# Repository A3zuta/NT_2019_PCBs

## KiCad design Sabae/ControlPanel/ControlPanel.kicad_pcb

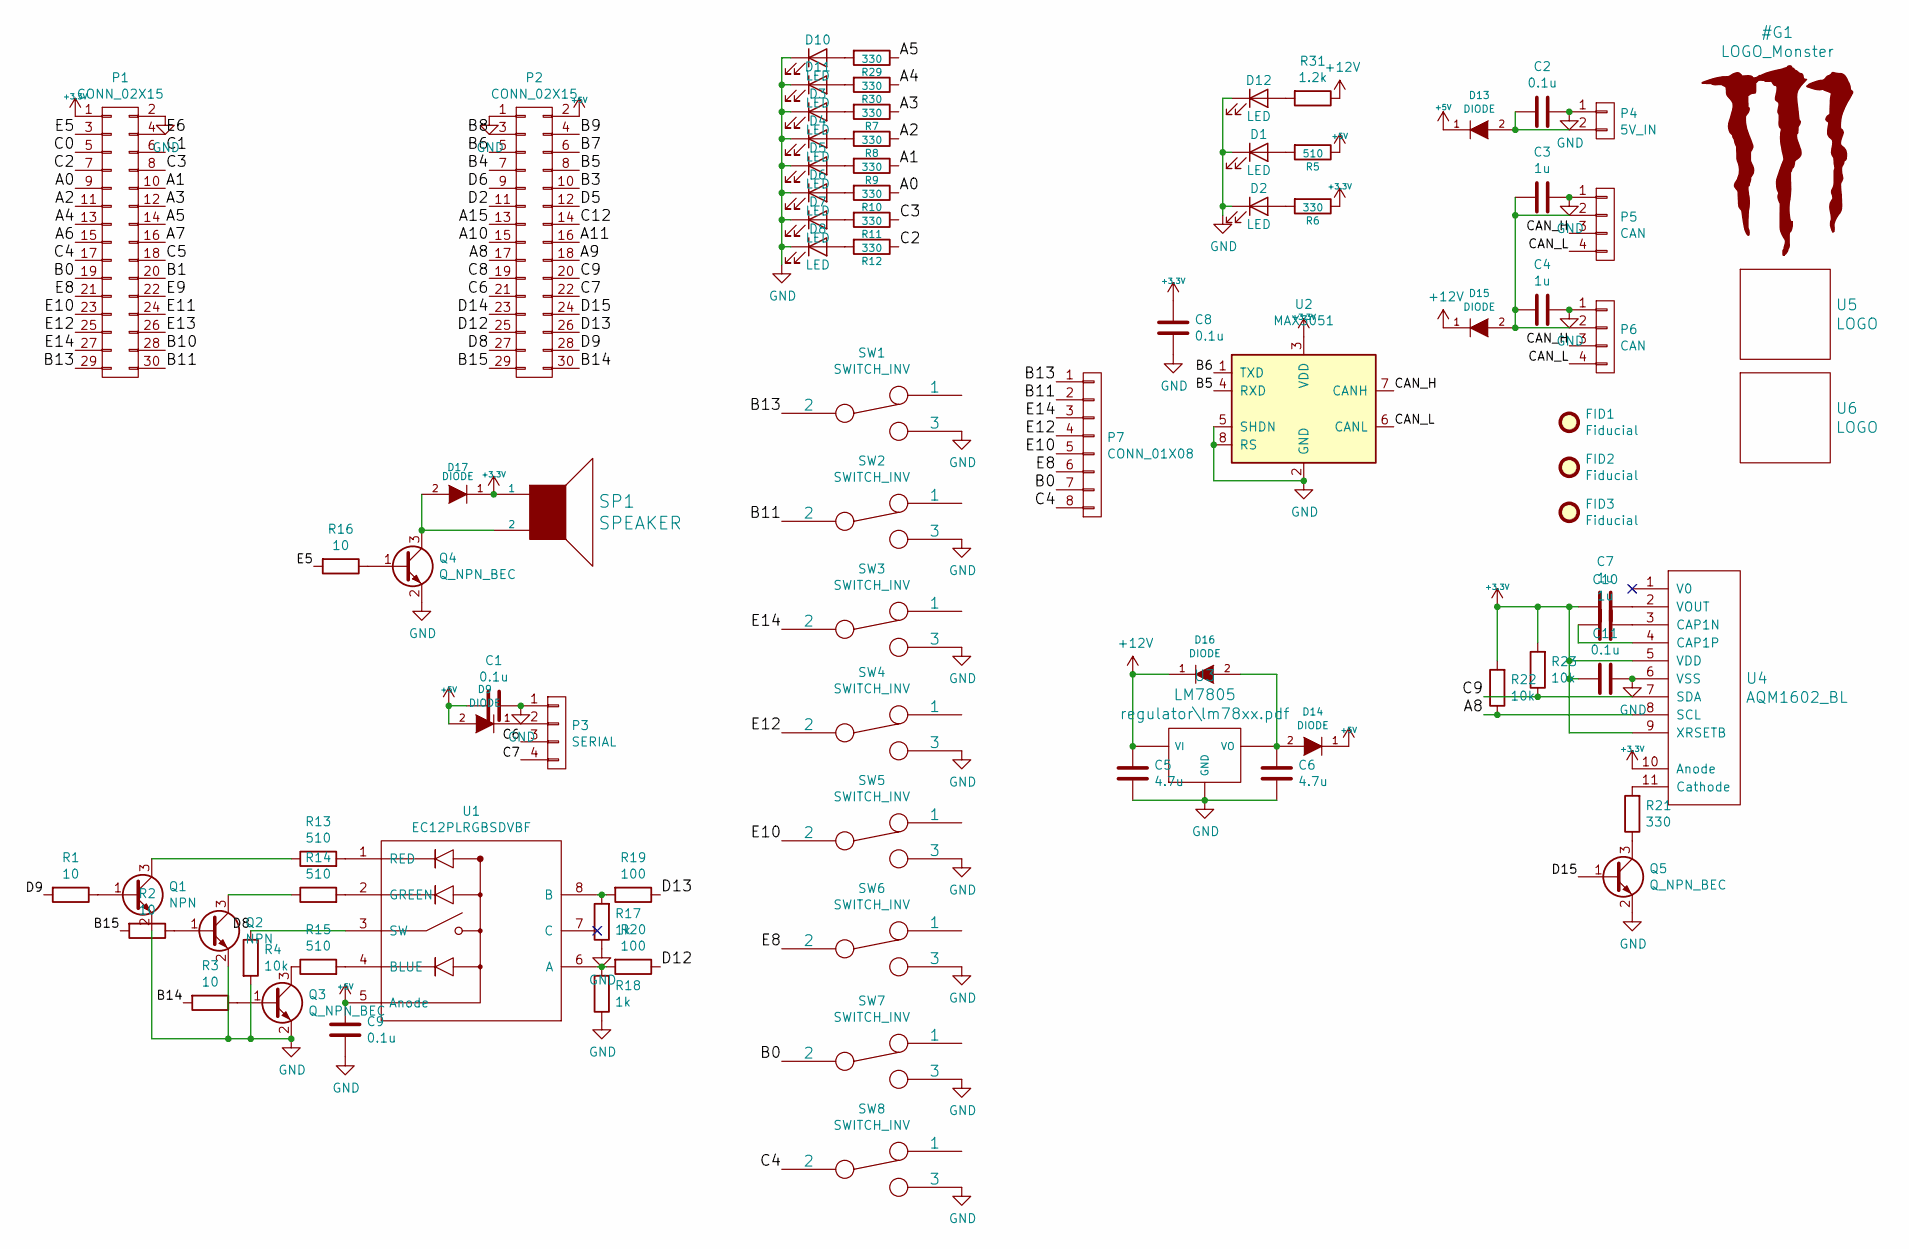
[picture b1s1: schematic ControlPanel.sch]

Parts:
C1, C2, C8, C9, C11: 0.1u; C_0603_1608Metric
C3, C4, C7, C10: 1u; C_0603_1608Metric
C5, C6: 4.7u; C_0805_2012Metric
D1, D2, D3, D4, D5, D6, D7, D8, D10, D11, D12: LED; LED_D3.0mm
D9, D13, D14, D15, D16, D17: DIODE; D_SOD-123
FID1, FID2, FID3: Fiducial; SW_28x11mm
P1, P2: CONN_02X15; PinSocket_2x15_P2.54mm_Vertical
P3: SERIAL; XA_4P
P4: 5V_IN; XA_2P
P5: CAN; XA_4P
P6: CAN; XA_4LC
P7: CONN_01X08; PinHeader_1x08_P2.54mm_Vertical
Q1, Q2: NPN; SOT-23W
Q3, Q4, Q5: Q_NPN_BEC; SOT-23W
R1, R2, R3, R16: 10; R_0603_1608Metric
R4, R22, R23: 10k; R_0603_1608Metric
R5, R13, R14, R15: 510; R_0603_1608Metric
R6, R7, R8, R9, R10, R11, R12, R21, R29, R30: 330; R_0603_1608Metric
R17, R18: 1k; R_0603_1608Metric
R19, R20: 100; R_0603_1608Metric
R31: 1.2k; R_0603_1608Metric
SP1: SPEAKER; UGCT7525AN4
SW1, SW2, SW3, SW4, SW5, SW6, SW7, SW8: SWITCH_INV; 2MS1-T1-B4-VS2-Q-E
U1: EC12PLRGBSDVBF
U2: MAX3051; SOIC-8_3.9x4.9mm_P1.27mm
U3: LM7805; TO-252-2
U4: AQM1602_BL; AQM1602_BL_Fad
U5: LOGO; Monster_Logo_F_CU
U6: LOGO; A.Mizuta_logo_15x9.1_F.CU

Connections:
+3V3: C7.2, C8.2, C11.2, D17.1 (K), P1.1, R6.1, R22.2, R23.2, SP1.1, U2.3 (VDD), U4.5 (VDD), U4.9 (XRSETB), U4.10 (Anode)
+5V: C1.2, C9.2, D9.2 (A), D13.1 (K), D14.1 (K), P2.2, R5.1, U1.5 (Anode)
+12V: C5.1, D15.1 (K), D16.1 (K), R31.1, U3.1 (VI)
/A0: P1.9, R10.1
/A1: P1.10, R9.1
/A2: P1.11, R8.1
/A3: P1.12, R7.1
/A4: P1.13, R30.1
/A5: P1.14, R29.1
/A6: P1.15
/A7: P1.16
/A8: P2.17, R22.1, U4.8 (SCL)
/A9: P2.18
/A10: P2.15
/A11: P2.16
/A15: P2.13
/B0: P1.19, P7.7, SW7.2
/B1: P1.20
/B3: P2.10
/B4: P2.7
/B5: P2.8, U2.4 (RXD)
/B6: P2.5, U2.1 (TXD)
/B7: P2.6
/B8: P2.3
/B9: P2.4
/B10: P1.28
/B11: P1.30, P7.2, SW2.2
/B13: P1.29, P7.1, SW1.2
/B14: P2.30, R3.2
/B15: P2.29, R2.2
/C0: P1.5
/C1: P1.6
/C2: P1.7, R12.1
/C3: P1.8, R11.1
/C4: P1.17, P7.8, SW8.2
/C5: P1.18
/C6: P2.21, P3.3
/C7: P2.22, P3.4
/C8: P2.19
/C9: P2.20, R23.1, U4.7 (SDA)
/C12: P2.14
/CAN_H: P5.3, P6.3, U2.7 (CANH)
/CAN_L: P5.4, P6.4, U2.6 (CANL)
/D2: P2.11
/D5: P2.12
/D6: P2.9
/D8: P2.27, R4.1, U1.3 (SW)
/D9: P2.28, R1.2
/D12: P2.25, R20.1
/D13: P2.26, R19.1
/D14: P2.23
/D15: P2.24, Q5.1 (B)
/E5: P1.3, R16.2
/E6: P1.4
/E8: P1.21, P7.6, SW6.2
/E9: P1.22
/E10: P1.23, P7.5, SW5.2
/E11: P1.24
/E12: P1.25, P7.4, SW4.2
/E13: P1.26
/E14: P1.27, P7.3, SW3.2
GND: C1.1, C2.1, C3.1, C4.1, C5.2, C6.2, C8.1, C9.1, C11.1, D1.1 (K), D2.1 (K), D3.1 (K), D4.1 (K), D5.1 (K), D6.1 (K), D7.1 (K), D8.1 (K), D10.1 (K), D11.1 (K), D12.1 (K), P1.2, P2.1, P3.1, P4.1, P5.1, P6.1, Q1.2 (E), Q2.2 (E), Q3.2 (E), Q4.2 (E), Q5.2 (E), R4.2, R17.1, R18.1, SW1.3, SW2.3, SW3.3, SW4.3, SW5.3, SW6.3, SW7.3, SW8.3, U2.2 (GND), U2.5 (SHDN), U2.8 (RS), U3.2 (GND), U4.6 (VSS)
unnamed: C2.2, D13.2 (A), P4.2
unnamed: C3.2, C4.2, D15.2 (A), P5.2, P6.2
unnamed: C6.1, D14.2 (A), D16.2 (A), U3.3 (VO)
unnamed: C7.1, U4.2 (VOUT)
unnamed: C10.1, U4.3 (CAP1N)
unnamed: C10.2, U4.4 (CAP1P)
unnamed: D1.2 (A), R5.2
unnamed: D2.2 (A), R6.2
unnamed: D3.2 (A), R7.2
unnamed: D4.2 (A), R8.2
unnamed: D5.2 (A), R9.2
unnamed: D6.2 (A), R10.2
unnamed: D7.2 (A), R11.2
unnamed: D8.2 (A), R12.2
unnamed: D9.1 (K), P3.2
unnamed: D10.2 (A), R29.2
unnamed: D11.2 (A), R30.2
unnamed: D12.2 (A), R31.2
unnamed: D17.2 (A), Q4.3 (C), SP1.2
unnamed: Q1.1 (B), R1.1
unnamed: Q1.3 (C), R13.1
unnamed: Q2.1 (B), R2.1
unnamed: Q2.3 (C), R14.1
unnamed: Q3.1 (B), R3.1
unnamed: Q3.3 (C), R15.1
unnamed: Q4.1 (B), R16.1
unnamed: Q5.3 (C), R21.1
unnamed: R13.2, U1.1 (RED)
unnamed: R14.2, U1.2 (GREEN)
unnamed: R15.2, U1.4 (BLUE)
unnamed: R17.2, R19.2, U1.8 (B)
unnamed: R18.2, R20.2, U1.6 (A)
unnamed: R21.2, U4.11 (Cathode)

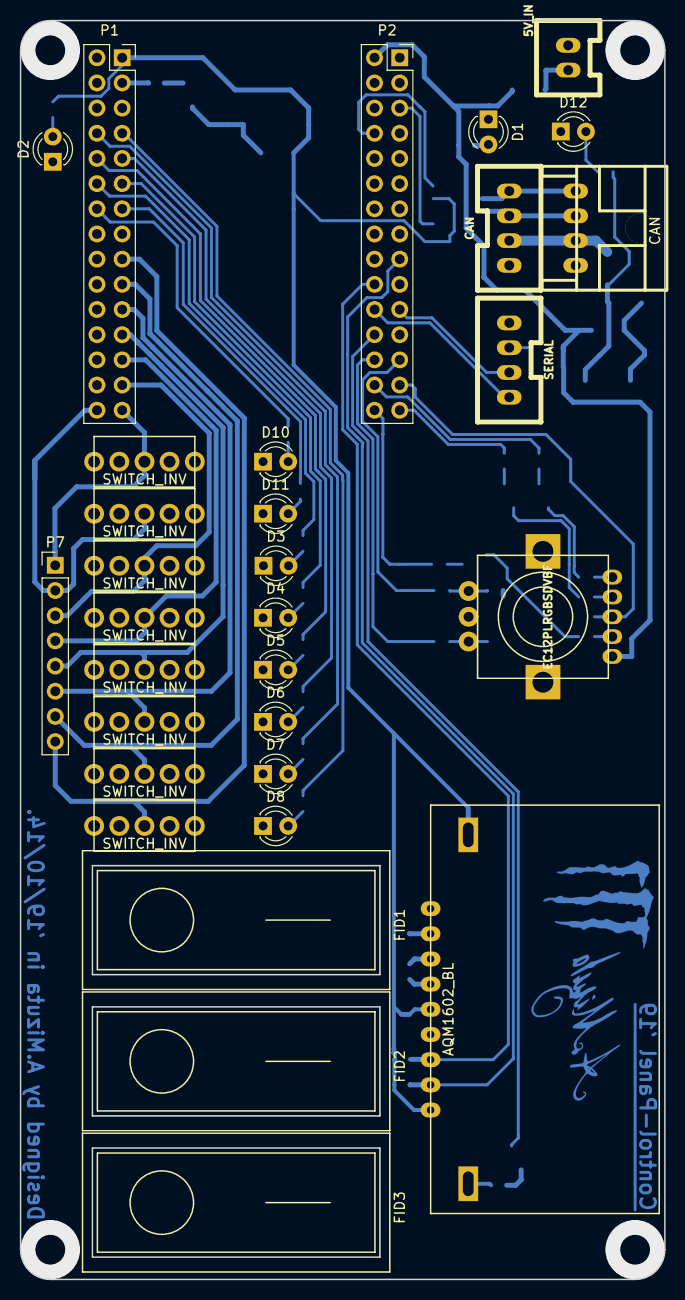
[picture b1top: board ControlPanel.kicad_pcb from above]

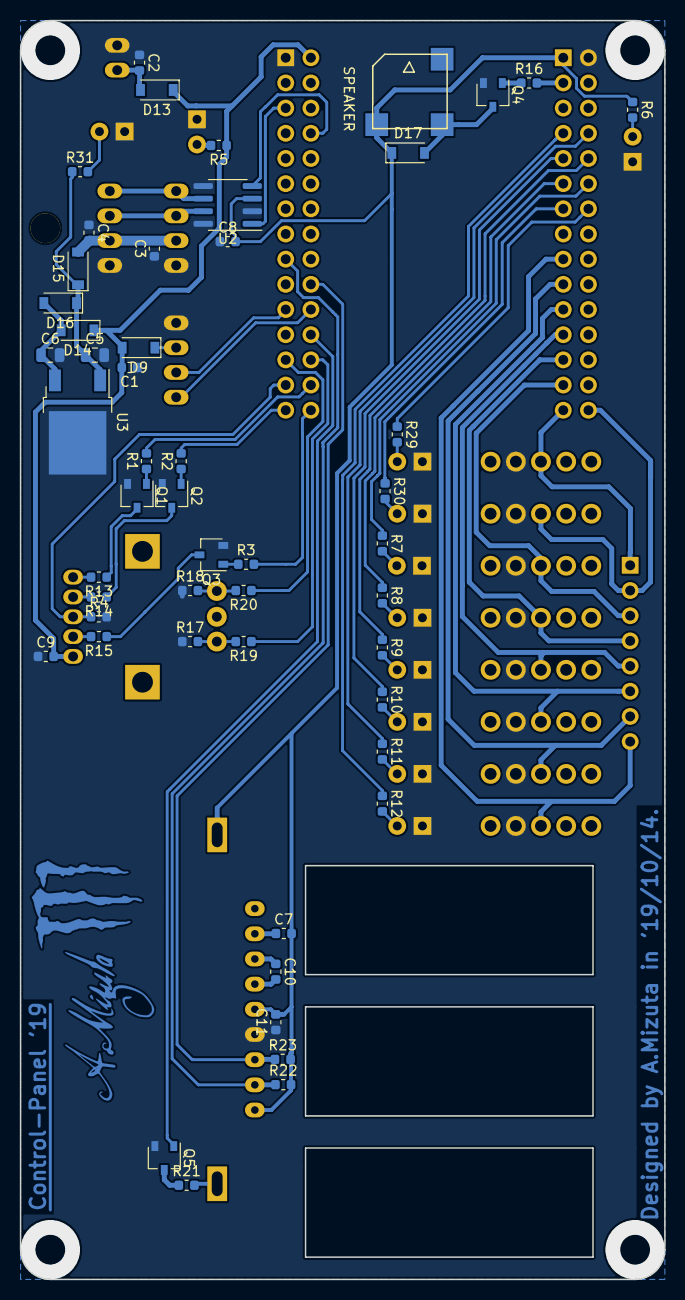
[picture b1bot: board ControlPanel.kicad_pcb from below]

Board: 2 copper layers, 65.0 x 127.0 mm, 84 parts (53 on the bottom side), 69 nets.

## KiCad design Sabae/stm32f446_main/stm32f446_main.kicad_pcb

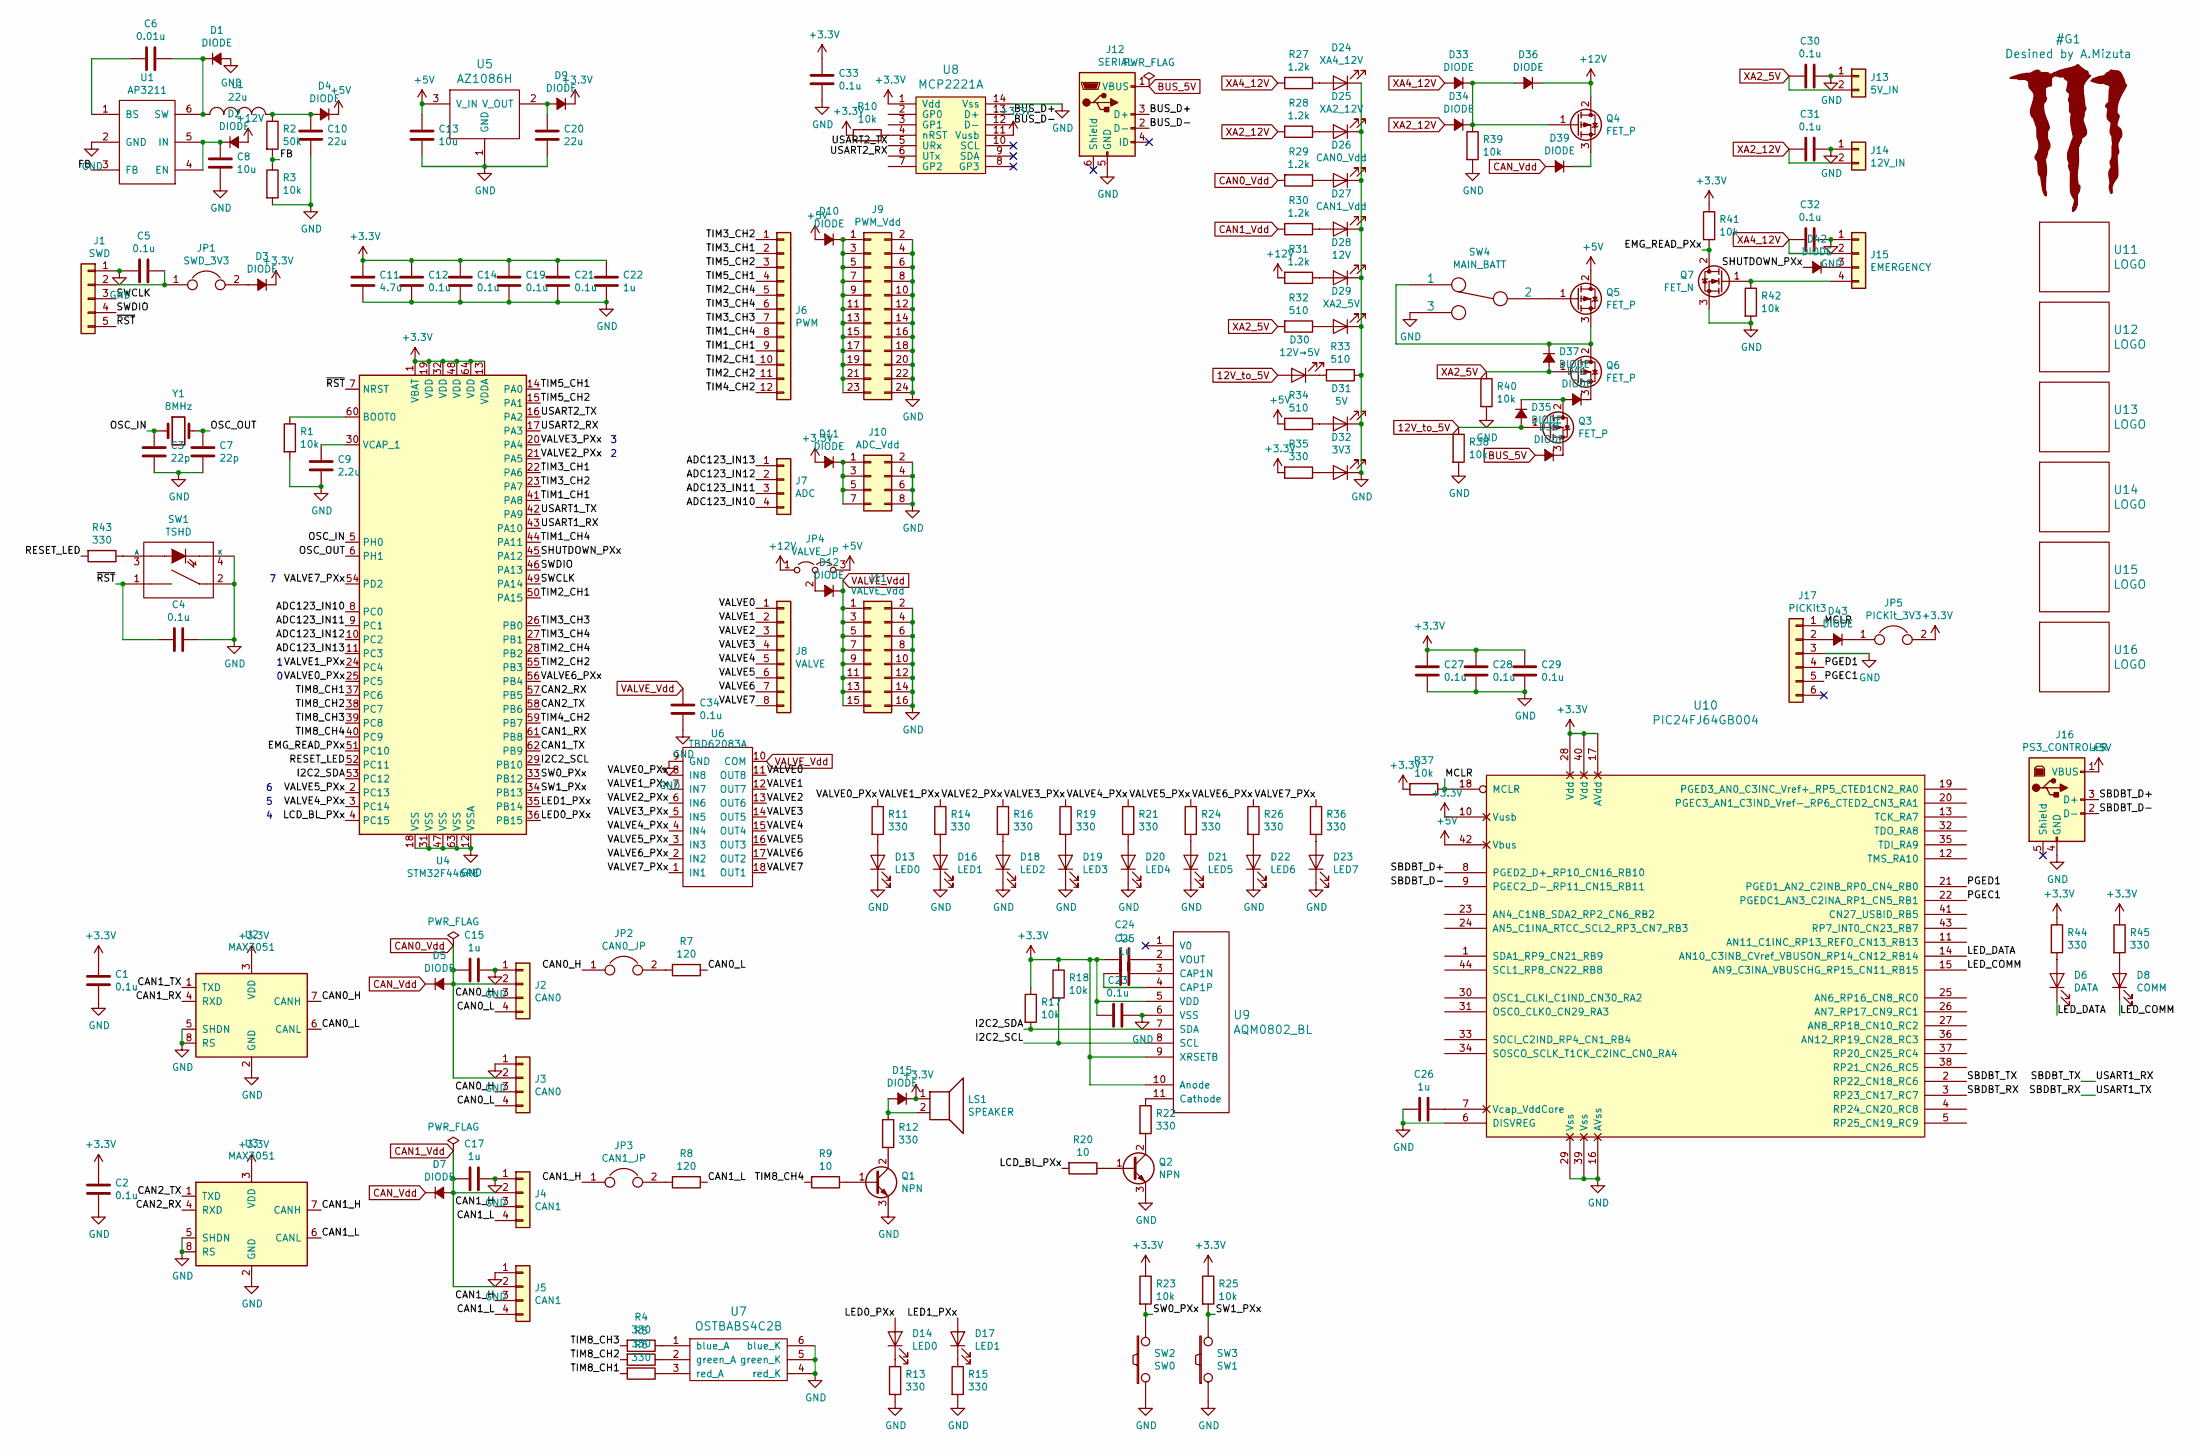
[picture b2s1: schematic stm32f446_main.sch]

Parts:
C1, C2, C4, C5, C12, C14, C19, C21, C23, C27, C28, C29, C30, C31, C32, C33, C34: 0.1u; C_0603_1608Metric
C3, C7: 22p; C_0603_1608Metric
C6: 0.01u; C_0603_1608Metric
C8, C13: 10u; C_0603_1608Metric
C9: 2.2u; C_0603_1608Metric
C10, C20: 22u; C_0603_1608Metric
C11: 4.7u; C_0603_1608Metric
C15, C17, C22, C24, C25, C26: 1u; C_0603_1608Metric
D1, D2, D3, D4, D5, D7, D9, D10, D11, D12, D15, D33, D34, D35, D36, D37, D38, D39, D41, D43: DIODE; D_SOD-123
D6: DATA; LED_0603_1608Metric
D8: COMM; LED_0603_1608Metric
D13, D14: LED0; LED_0603_1608Metric
D16, D17: LED1; LED_0603_1608Metric
D18: LED2; LED_0603_1608Metric
D19: LED3; LED_0603_1608Metric
D20: LED4; LED_0603_1608Metric
D21: LED5; LED_0603_1608Metric
D22: LED6; LED_0603_1608Metric
D23: LED7; LED_0603_1608Metric
D24: XA4_12V; LED_0603_1608Metric
D25: XA2_12V; LED_0603_1608Metric
D26: CAN0_Vdd; LED_0603_1608Metric
D27: CAN1_Vdd; LED_0603_1608Metric
D28: 12V; LED_0603_1608Metric
D29: XA2_5V; LED_0603_1608Metric
D30: 12V→5V; LED_0603_1608Metric
D31: 5V; LED_0603_1608Metric
D32: 3V3; LED_0603_1608Metric
D42: DIODE; D_0603_1608Metric
J1: SWD; PinHeader_1x05_P2.54mm_Vertical
J2: CAN0; XA_4P
J3: CAN0; XA_4LC
J4: CAN1; XA_4P
J5: CAN1; XA_4LC
J6: PWM; PinHeader_1x12_P2.54mm_Vertical
J7: ADC; PinHeader_1x04_P2.54mm_Vertical
J8: VALVE; PinHeader_1x08_P2.54mm_Vertical
J9: PWM_Vdd; PinHeader_2x12_P2.54mm_Vertical
J10: ADC_Vdd; PinHeader_2x04_P2.54mm_Vertical
J11: VALVE_Vdd; PinHeader_2x08_P2.54mm_Vertical
J12: SERIAL; USB_Micro-B_Molex_47346-0001
J13: 5V_IN; XA_2P
J14: 12V_IN; XA_2P
J15: EMERGENCY; XA_4LC
J16: PS3_CONTROLER; USB_A
J17: PICKit3; ZH_6P
JP1: SWD_3V3; SolderJumper-2_P1.3mm_Open_TrianglePad1.0x1.5mm
JP2: CAN0_JP; PinHeader_1x02_P2.54mm_Vertical
JP3: CAN1_JP; PinHeader_1x02_P2.54mm_Vertical
JP4: VALVE_JP; SolderJumper-3_P2.0mm_Open_TrianglePad1.0x1.5mm
JP5: PICKit_3V3; SolderJumper-2_P1.3mm_Open_TrianglePad1.0x1.5mm
L1: 22u; Inductor_Taiyo-Yuden_NR-50xx_HandSoldering
LS1: SPEAKER; UGCT7525AN4
Q1, Q2: NPN; SOT-23W
Q3, Q4, Q5, Q6: FET_P; SOT-23W
Q7: FET_N; SOT-23W
R1, R3, R10, R17, R18, R23, R25, R37, R38, R39, R40, R41, R42: 10k; R_0603_1608Metric
R2: 50k; R_0603_1608Metric
R4, R5, R6, R11, R12, R13, R14, R15, R16, R19, R21, R22, R24, R26, R35, R36, R43, R44, R45: 330; R_0603_1608Metric
R7, R8: 120; R_0603_1608Metric
R9, R20: 10; R_0603_1608Metric
R27, R28, R29, R30, R31: 1.2k; R_0603_1608Metric
R32, R33, R34: 510; R_0603_1608Metric
SW1: TSHD
SW2: SW0; SW_SPST_CK_RS282G05A3
SW3: SW1; SW_SPST_CK_RS282G05A3
SW4: MAIN_BATT; 2MS1-T1-B4-VS2-Q-E
U1: AP3211; TSOP-6_1.65x3.05mm_P0.95mm
U2, U3: MAX3051; SOIC-8_3.9x4.9mm_P1.27mm
U4: STM32F446RE; LQFP-64_10x10mm_P0.5mm
U5: AZ1086H; SOT-223-3_TabPin2
U6: TBD62083A; SOIC-18W_7.5x11.6mm_P1.27mm
U7: OSTBABS4C2B
U8: MCP2221A; SOIC-14_3.9x8.7mm_P1.27mm
U9: AQM0802_BL; AQM1602_BL_Fad
U10: PIC24FJ64GB004; LQFP-44_10x10mm_P0.8mm
U11: LOGO; Mini_Monster
U12: LOGO; NT_2019_Logo_5.0x5.0_Mask
U13: LOGO; Amethyst_logo10x11_silk
U14: LOGO; Information_logo_3x3_silk
U15: LOGO; Infomation_QR_14.5x14.5_silk
U16: LOGO; Information_logo_5x5_silk
Y1: 8MHz; Crystal_SMD_5032_2Pads

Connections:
12V_to_5V: D30.2 (A), D35.2 (A), Q3.1 (G), R38.1
+3V3: C1.1, C2.1, C11.1, C12.1, C14.1, C19.1, C21.1, C22.1, C23.2, C24.2, C27.1, C28.1, C29.1, C33.1, D3.1 (K), D9.1 (K), D11.2 (A), D15.1 (K), JP5.2, LS1.1, R10.2, R17.1, R18.1, R23.1, R25.1, R35.2, R37.2, R41.1, R44.1, R45.1, U2.3 (VDD), U3.3 (VDD), U4.1 (VBAT), U4.13 (VDDA), U4.19 (VDD), U4.32 (VDD), U4.48 (VDD), U4.64 (VDD), U8.1 (Vdd), U8.11 (Vusb), U9.5 (VDD), U9.9 (XRSETB), U9.10 (Anode), U10.10 (Vusb), U10.17 (AVdd), U10.28 (Vdd), U10.40 (Vdd)
+5V: C13.1, D4.1 (K), D10.2 (A), J16.1 (VBUS), JP4.3 (B), Q5.2 (D), R34.2, U5.3 (V_IN), U10.42 (Vbus)
+12V: D2.2 (A), D36.1 (K), JP4.1 (A), Q4.2 (D), R31.2
/ADC123_IN10: J7.4, U4.8 (PC0)
/ADC123_IN11: J7.3, U4.9 (PC1)
/ADC123_IN12: J7.2, U4.10 (PC2)
/ADC123_IN13: J7.1, U4.11 (PC3)
/BUS_D+: J12.3 (D+), U8.13 (D+)
/BUS_D-: J12.2 (D-), U8.12 (D-)
/CAN0_H: J2.3, J3.3, JP2.1, U2.7 (CANH)
/CAN0_L: J2.4, J3.4, R7.1, U2.6 (CANL)
/CAN1_H: J4.3, J5.3, JP3.1, U3.7 (CANH)
/CAN1_L: J4.4, J5.4, R8.1, U3.6 (CANL)
/CAN1_RX: U2.4 (RXD), U4.61 (PB8)
/CAN1_TX: U2.1 (TXD), U4.62 (PB9)
/CAN2_RX: U3.4 (RXD), U4.57 (PB5)
/CAN2_TX: U3.1 (TXD), U4.58 (PB6)
/EMG_READ_PXx: Q7.2 (D), R41.2, U4.51 (PC10)
/FB: R2.2, R3.1, U1.3 (FB)
/I2C2_SCL: R18.2, U4.29 (PB10), U9.8 (SCL)
/I2C2_SDA: R17.2, U4.53 (PC12), U9.7 (SDA)
/LCD_BL_PXx: R20.2, U4.4 (PC15)
/LED0_PXx: D14.2 (A), U4.36 (PB15)
/LED1_PXx: D17.2 (A), U4.35 (PB14)
/LED_COMM: D8.1 (K), U10.15 (AN9_C3INA_VBUSCHG_RP15_CN11_RB15)
/LED_DATA: D6.1 (K), U10.14 (AN10_C3INB_CVref_VBUSON_RP14_CN12_RB14)
/MCLR: J17.1, R37.1, U10.18 (MCLR)
/OSC_IN: C3.1, U4.5 (PH0), Y1.1
/OSC_OUT: C7.1, U4.6 (PH1), Y1.2
/PGEC1: J17.5, U10.22 (PGEDC1_AN3_C2INA_RP1_CN5_RB1)
/PGED1: J17.4, U10.21 (PGED1_AN2_C2INB_RP0_CN4_RB0)
/RESET_LED: R43.2, U4.52 (PC11)
/SBDBT_D+: J16.3 (D+), U10.8 (PGED2_D+_RP10_CN16_RB10)
/SBDBT_D-: J16.2 (D-), U10.9 (PGEC2_D-_RP11_CN15_RB11)
/SBDBT_RX: U4.42 (PA9), U10.3 (RP23_CN17_RC7)
/SBDBT_TX: U4.43 (PA10), U10.2 (RP22_CN18_RC6)
/SHUTDOWN_PXx: D42.2 (A), U4.45 (PA12)
/SW0_PXx: R23.2, SW2.2, U4.33 (PB12)
/SW1_PXx: R25.2, SW3.2, U4.34 (PB13)
/SWCLK: J1.3, U4.49 (PA14)
/SWDIO: J1.4, U4.46 (PA13)
/TIM1_CH1: J6.9, U4.41 (PA8)
/TIM1_CH4: J6.8, U4.44 (PA11)
/TIM2_CH1: J6.10, U4.50 (PA15)
/TIM2_CH2: J6.11, U4.55 (PB3)
/TIM2_CH4: J6.5, U4.28 (PB2)
/TIM3_CH1: J6.2, U4.22 (PA6)
/TIM3_CH2: J6.1, U4.23 (PA7)
/TIM3_CH3: J6.7, U4.26 (PB0)
/TIM3_CH4: J6.6, U4.27 (PB1)
/TIM4_CH2: J6.12, U4.59 (PB7)
/TIM5_CH1: J6.4, U4.14 (PA0)
/TIM5_CH2: J6.3, U4.15 (PA1)
/TIM8_CH1: R6.2, U4.37 (PC6)
/TIM8_CH2: R5.2, U4.38 (PC7)
/TIM8_CH3: R4.2, U4.39 (PC8)
/TIM8_CH4: R9.2, U4.40 (PC9)
/USART2_RX: U4.17 (PA3), U8.6 (UTx)
/USART2_TX: U4.16 (PA2), U8.5 (URx)
/VALVE0: J8.1, U6.11 (OUT8)
/VALVE0_PXx: R11.1, U4.25 (PC5), U6.8 (IN8)
/VALVE1: J8.2, U6.12 (OUT7)
/VALVE1_PXx: R14.1, U4.24 (PC4), U6.7 (IN7)
/VALVE2: J8.3, U6.13 (OUT6)
/VALVE2_PXx: R16.1, U4.21 (PA5), U6.6 (IN6)
/VALVE3: J8.4, U6.14 (OUT5)
/VALVE3_PXx: R19.1, U4.20 (PA4), U6.5 (IN5)
/VALVE4: J8.5, U6.15 (OUT4)
/VALVE4_PXx: R21.1, U4.3 (PC14), U6.4 (IN4)
/VALVE5: J8.6, U6.16 (OUT3)
/VALVE5_PXx: R24.1, U4.2 (PC13), U6.3 (IN3)
/VALVE6: J8.7, U6.17 (OUT2)
/VALVE6_PXx: R26.1, U4.56 (PB4), U6.2 (IN2)
/VALVE7: J8.8, U6.18 (OUT1)
/VALVE7_PXx: R36.1, U4.54 (PD2), U6.1 (IN1)
/~RST: C4.1, J1.5, SW1.1, U4.7 (NRST)
BUS_5V: D38.2 (A), J12.1 (VBUS)
CAN0_Vdd: C15.2, D5.2 (A), J2.2, J3.2, R29.2
CAN1_Vdd: C17.2, D7.2 (A), J4.2, J5.2, R30.2
CAN_Vdd: D5.1 (K), D7.1 (K), D39.2 (A)
GND: C1.2, C2.2, C3.2, C4.2, C5.2, C7.2, C8.2, C9.2, C10.2, C11.2, C12.2, C13.2, C14.2, C15.1, C17.1, C19.2, C20.2, C21.2, C22.2, C23.1, C26.2, C27.2, C28.2, C29.2, C30.1, C31.1, C32.1, C33.2, C34.2, D1.2 (A), D13.1 (K), D16.1 (K), D18.1 (K), D19.1 (K), D20.1 (K), D21.1 (K), D22.1 (K), D23.1 (K), D24.1 (K), D25.1 (K), D26.1 (K), D27.1 (K), D28.1 (K), D29.1 (K), D31.1 (K), D32.1 (K), J1.1, J2.1, J3.1, J4.1, J5.1, J9.2, J9.4, J9.6, J9.8, J9.10, J9.12, J9.14, J9.16, J9.18, J9.20, J9.22, J9.24, J10.2, J10.4, J10.6, J10.8, J11.2, J11.4, J11.6, J11.8, J11.10, J11.12, J11.14, J11.16, J12.5 (GND), J13.1, J14.1, J15.1, J16.4 (GND), J17.3, Q1.3 (E), Q2.3 (E), Q7.3 (S), R1.2, R3.2, R13.2, R15.2, R33.1, R38.2, R39.2, R40.2, R42.2, SW1.2, SW1.4 (K), SW2.1, SW3.1, SW4.3, U1.2 (GND), U2.2 (GND), U2.5 (SHDN), U2.8 (RS), U3.2 (GND), U3.5 (SHDN), U3.8 (RS), U4.12 (VSSA), U4.18 (VSS), U4.31 (VSS), U4.47 (VSS), U4.63 (VSS), U5.1 (GND), U6.9 (GND), U7.4 (red_K), U7.5 (green_K), U7.6 (blue_K), U8.14 (Vss), U9.6 (VSS), U10.6 (DISVREG), U10.16 (AVss), U10.29 (Vss), U10.39 (Vss)
unnamed: C5.1, J1.2, JP1.1
unnamed: C6.1, D1.1 (K), L1.1, U1.6 (SW)
unnamed: C6.2, U1.1 (BS)
unnamed: C8.1, D2.1 (K), U1.4 (EN), U1.5 (IN)
unnamed: C9.1, U4.30 (VCAP_1)
unnamed: C10.1, D4.2 (A), L1.2, R2.1
unnamed: C20.1, D9.2 (A), U5.2 (V_OUT)
unnamed: C24.1, U9.2 (VOUT)
unnamed: C25.1, U9.3 (CAP1N)
unnamed: C25.2, U9.4 (CAP1P)
unnamed: C26.1, U10.7 (Vcap_VddCore)
unnamed: D3.2 (A), JP1.2
unnamed: D6.2 (A), R44.2
unnamed: D8.2 (A), R45.2
unnamed: D10.1 (K), J9.1, J9.3, J9.5, J9.7, J9.9, J9.11, J9.13, J9.15, J9.17, J9.19, J9.21, J9.23
unnamed: D11.1 (K), J10.1, J10.3, J10.5, J10.7
unnamed: D12.2 (A), JP4.2 (C)
unnamed: D13.2 (A), R11.2
unnamed: D14.1 (K), R13.1
unnamed: D15.2 (A), LS1.2, R12.1
unnamed: D16.2 (A), R14.2
unnamed: D17.1 (K), R15.1
unnamed: D18.2 (A), R16.2
unnamed: D19.2 (A), R19.2
unnamed: D20.2 (A), R21.2
unnamed: D21.2 (A), R24.2
unnamed: D22.2 (A), R26.2
unnamed: D23.2 (A), R36.2
unnamed: D24.2 (A), R27.1
unnamed: D25.2 (A), R28.1
unnamed: D26.2 (A), R29.1
unnamed: D27.2 (A), R30.1
unnamed: D28.2 (A), R31.1
unnamed: D29.2 (A), R32.1
unnamed: D30.1 (K), R33.2
unnamed: D31.2 (A), R34.1
unnamed: D32.2 (A), R35.1
unnamed: D33.1 (K), D34.1 (K), D36.2 (A), Q4.1 (G), R39.1
unnamed: D35.1 (K), D41.2 (A), Q3.2 (D)
unnamed: D37.1 (K), Q5.3 (S), Q6.2 (D), SW4.1
unnamed: D38.1 (K), Q3.3 (S)
unnamed: D39.1 (K), Q4.3 (S)
unnamed: D41.1 (K), Q6.3 (S)
unnamed: D42.1 (K), J15.3
unnamed: D43.1 (K), JP5.1
unnamed: D43.2 (A), J17.2
unnamed: J15.4, Q7.1 (G), R42.1
unnamed: JP2.2, R7.2
unnamed: JP3.2, R8.2
unnamed: Q1.1 (B), R9.1
unnamed: Q1.2 (C), R12.2
unnamed: Q2.1 (B), R20.1
unnamed: Q2.2 (C), R22.2
unnamed: Q5.1 (G), SW4.2
unnamed: R1.1, U4.60 (BOOT0)
unnamed: R4.1, U7.1 (blue_A)
unnamed: R5.1, U7.2 (green_A)
unnamed: R6.1, U7.3 (red_A)
unnamed: R10.1, U8.4 (nRST)
unnamed: R22.1, U9.11 (Cathode)
unnamed: R43.1, SW1.3 (A)
VALVE_Vdd: C34.1, D12.1 (K), J11.1, J11.3, J11.5, J11.7, J11.9, J11.11, J11.13, J11.15, U6.10 (COM)
XA2_5V: C30.2, D37.2 (A), J13.2, Q6.1 (G), R32.2, R40.1
XA2_12V: C31.2, D34.2 (A), J14.2, R28.2
XA4_12V: C32.2, D33.2 (A), J15.2, R27.2

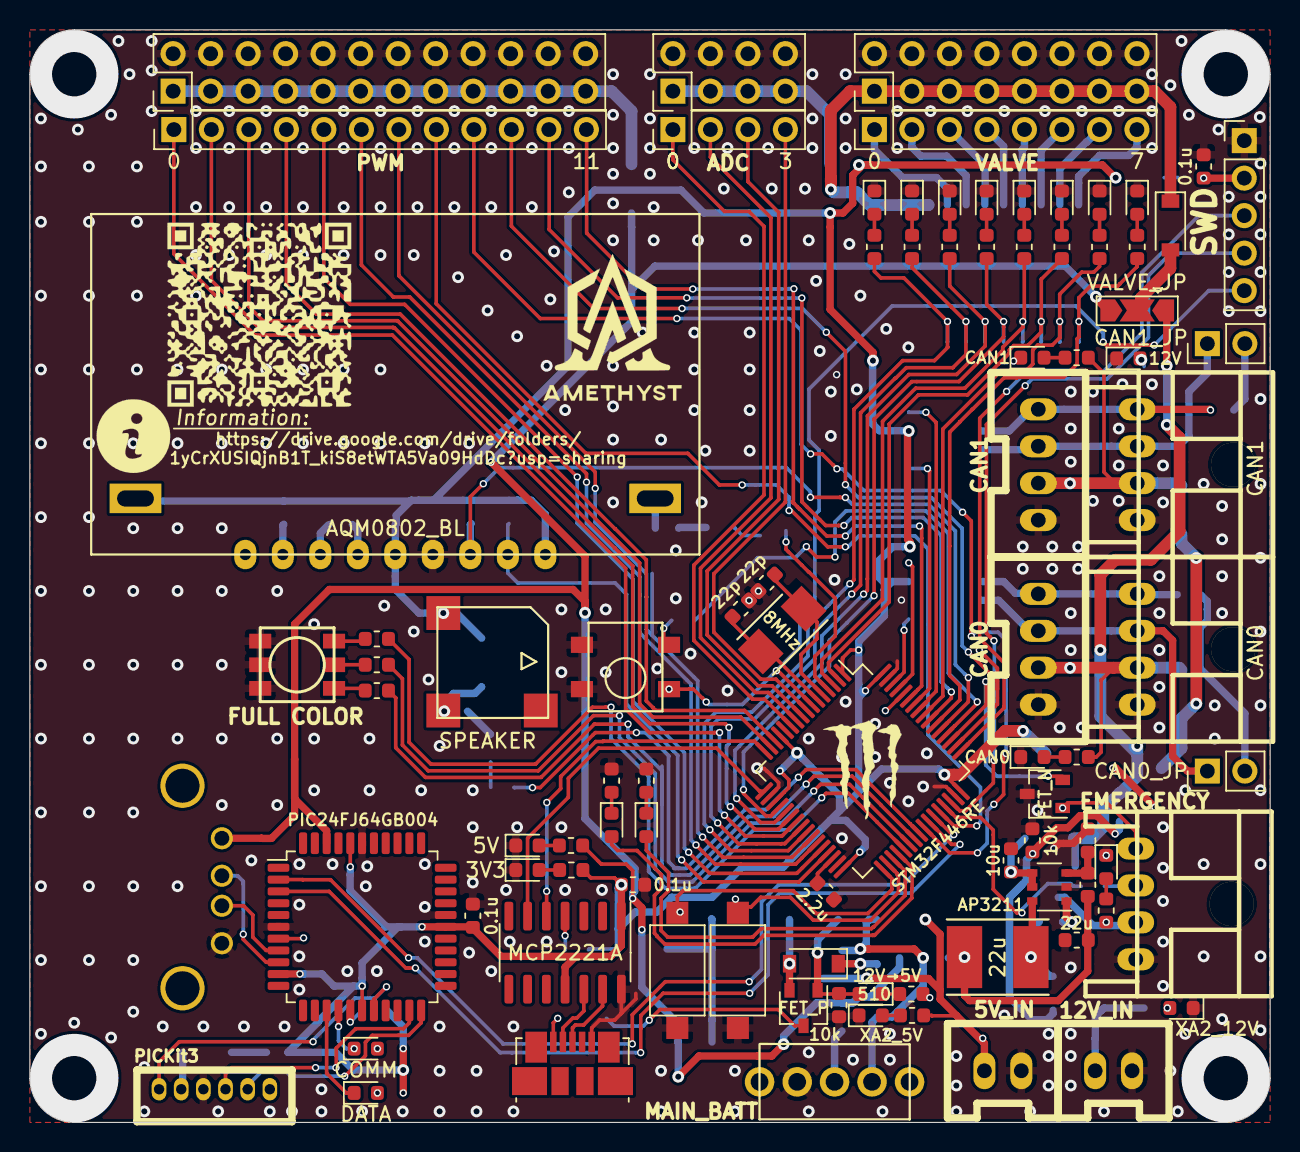
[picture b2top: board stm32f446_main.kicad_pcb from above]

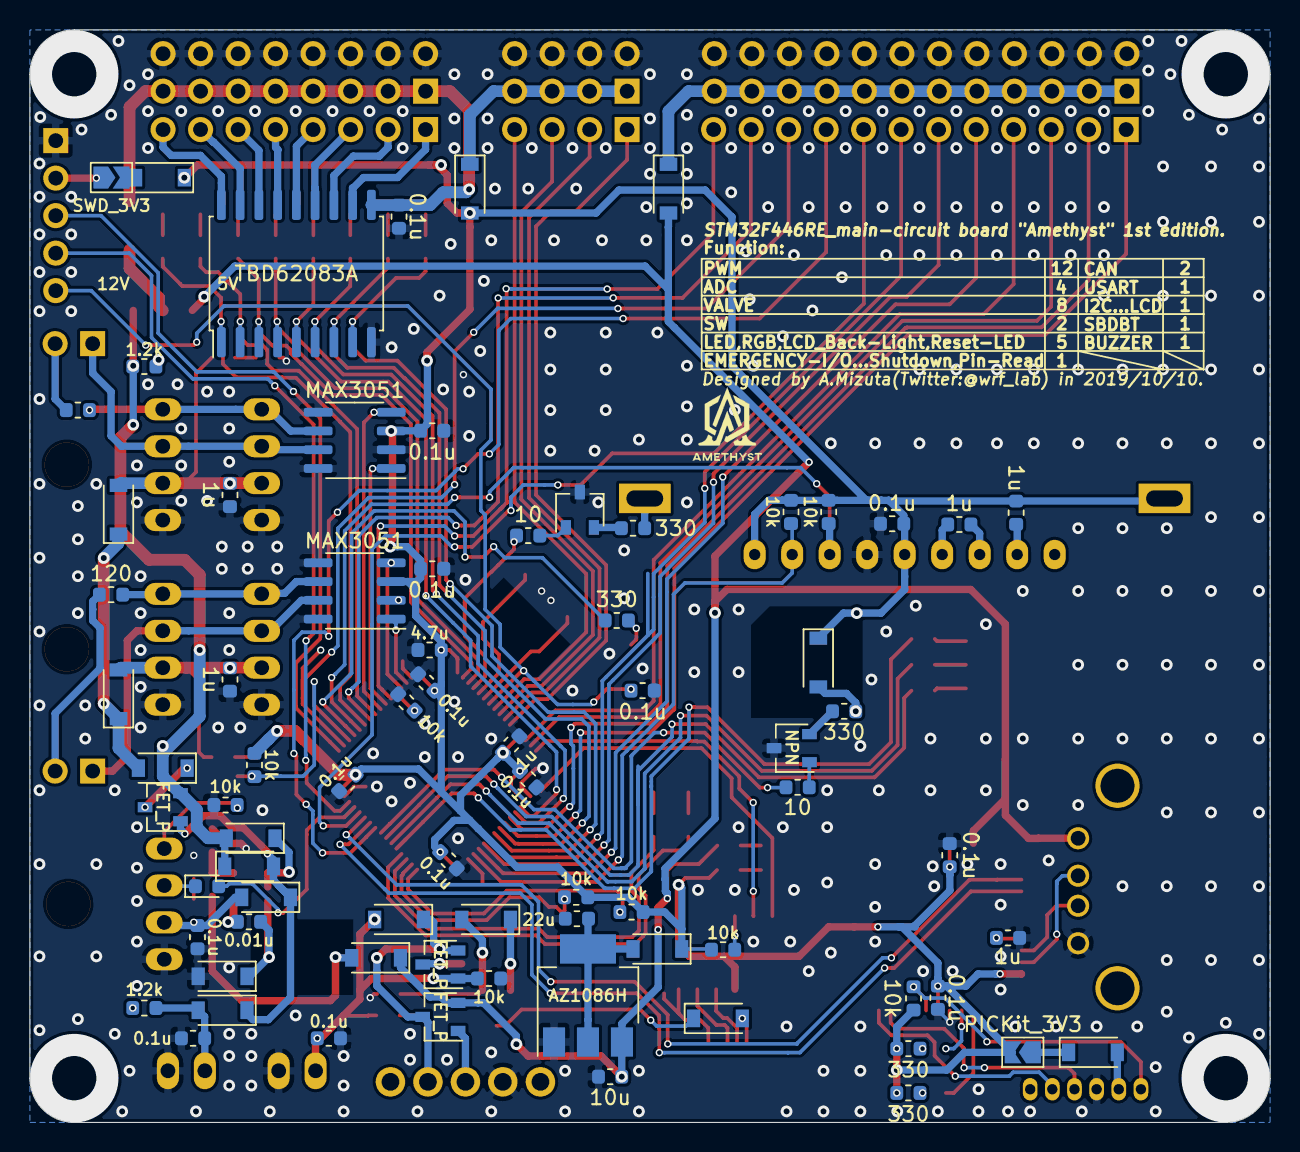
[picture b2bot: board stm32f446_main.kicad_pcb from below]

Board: 2 copper layers, 84.0 x 74.0 mm, 171 parts (76 on the bottom side), 147 nets.
